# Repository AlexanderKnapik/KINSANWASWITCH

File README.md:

# KINSANWASWITCH

DIY-friendly photointerrupter microswitch/lamp holder 2-in-1 for generic 100mm Chinese arcade buttons. Enables an OBSA-LHSXF+OBSA-100UMQ-like setup at low cost with generic parts.

## Updates
- This is branch of beta-version SHINSANWASWITCH update version 1.1 with some optimizations that needs to be verified, so now everything is divided into two branches: *main* with stable version 1.0 and version1.1 in *beta* . If you want currently stable version - use *main* branch. 
Version 1.1 has some optimizations in body of SHINSANWASWITCH and possibility to make different variants of PCB to make with possibility to make one-layered-board at home (if you have enough skill). More info here:  https://www.projectdiva.net/community/threads/shinsanwaswitch-blog-of-creating-diy-analog-of-obsa-lhsxf-ln.2325/page-2#post-18644

## Parts list

### Electrical
Details about PCB and it's variants can be found in [readme in pcb thread](pcb/README.md)

- PCB: 1x `PCB` **1mm thickness** (KiCad 5.99+ (5.99.0-12455-g28bd734313), release build required for exporting Gerber files or take Gerber files archive in `gerber/shinsanwaswitch.zip`)
  - C1: Generic 0.1uF through hole ceramic capacitor.
  - C2: *not necessary, but recommended* 47uF 6.3v electrolitic capacitor on the power line input (read [some nuances of board assembly](https://github.com/steelpuxnastik/SHINSANWASWITCH/tree/version1.1/pcb#some-nuances-of-board-assembly) for more ditails)
  - STI1: `NSI45020AT1G` (for standard and one-layered-board with LED driver board versions) or R4: 470ohm 5% 1/4W through hole (for one-layered-board with resistor and 12v power-up 20mA LED, in other case use calculation to know what resistor you need to use)
  - J1: `S5B-PH-K-S` or equivalent.
  - LED: `S2B-PH-K-S` or equivalent.
  - PC1: `RPI-352`.
  - Q1: `2SC5395-F` or equivalent (may be rare but can be found on e.g. aliexpress).
  - R1: 330ohm 5% 1/4W through hole.
  - R2: 22kohm 5% 1/4W through hole.
  - R3: 10kohm 5% 1/4W through hole.
- 1x harness
  - 5x Single-ended **JST PH** wires (can be found on e.g. aliexpress or alternatively you can crimp them yourself, I recommend you to found on aliexpress for it 5pin 22 AWG white-blue-red-green-black cable, it amazingly fits connector, feels very reliable and also fits into the understandable color scheme)
  - 1x JST `PHR-5` or equivalent.
- 1x LED assembly (no resistors required)
  - 2x **JST PH** to **.1" (BLS-02/Dupont 2pin) female** wires (can be found on e.g. aliexpress or alternatively you can crimp them yourself. I recommend to use wires flexible as possible, that will be very useful. Wires length - somewhere around ~150-160mm, need be shorter as possible, because long wires will be nowhere to fold. Can be made by soldering single-ended JST PH wire and .1" (BLS-02/Dupont 2pin) female wire together and wrapping each wire with heat shrink tubing).
  - 1x 20mA through hole white LED (plugs into the .1" (BLS-02/Dupont 2pin) female connector).
  - 1x JST `PHR-2` or equivalent.
  - 1x 2 pin .1" (BLS-02/Dupont 2pin) female connector housing.
  
### Pin mapping

I/O port (from up to down):

| \#  | Description |
| --- | ----------- |
|  1  | LED+ |
|  2  | LED- |
|  3  | +5V |
|  4  | OUT |
|  5  | GND |

LED connector (from up to down):

| \#  | Description |
| --- | ----------- |
|  1  | + |
|  2  | - |

### Mechanical

- 3D printable parts (printing in resin recommended for best accuracy but not required)
  - 1x `STL/body.STL`
  - 1x `STL/cap.STL`
  - 3x `STL/lever_*.STL` (because of possible differences of generic 100mm Chinese arcade buttons and possible differences in preferences of players that will use it there available 3 different lengts of levers that you should print separately (and better in different colors) and then determine from your own experience what is best for you)
	- 1x `STL/lever_long.STL`
	- 1x `STL/lever_middle.STL`
	- 1x `STL/lever_short.STL`
- 1x 0.3x6x10mm (wire thickness x outer diameter x length) spring (can be found on e.g. aliexpress).
- 2x M2x8 screws

### Example of 3D-print settings that were used
- Layer height: 0.12mm (can be less, but not more, because quality depends on it)
- Nozzle: 0,4mm (can be less, of course)
- Fill level: 25%
- Number of wall lines: 4
- Number of cover layers: 4
- Number of bottom layers: 4
- Supports: only from the bed
- Filament: PETG
- Color: any, but the lever must be black or the part of lever that crosses the optocoupler must be painted with a marker in black in several layers, otherwise the optocoupler will work incorrectly and the switch will not work correctly.

## Source files
In folder `source` there are available source files that used to create 3D-models in SolidWorks. You can use them to make your modification, if you need it.

Original 100mm arcade button Solidworks source files taken from https://grabcad.com/library/100mm-button-1 and very helped me to make this thing.

# Known issues 
At this moment there is no possibility to connect SHINSANWASWITCH (and its active board) to regular matrices, where used connection between different pins, but not pin to ground that used here. If you know how to get around this problem - please, write about that in our issues thread: https://github.com/steelpuxnastik/SHINSANWASWITCH/issues/1

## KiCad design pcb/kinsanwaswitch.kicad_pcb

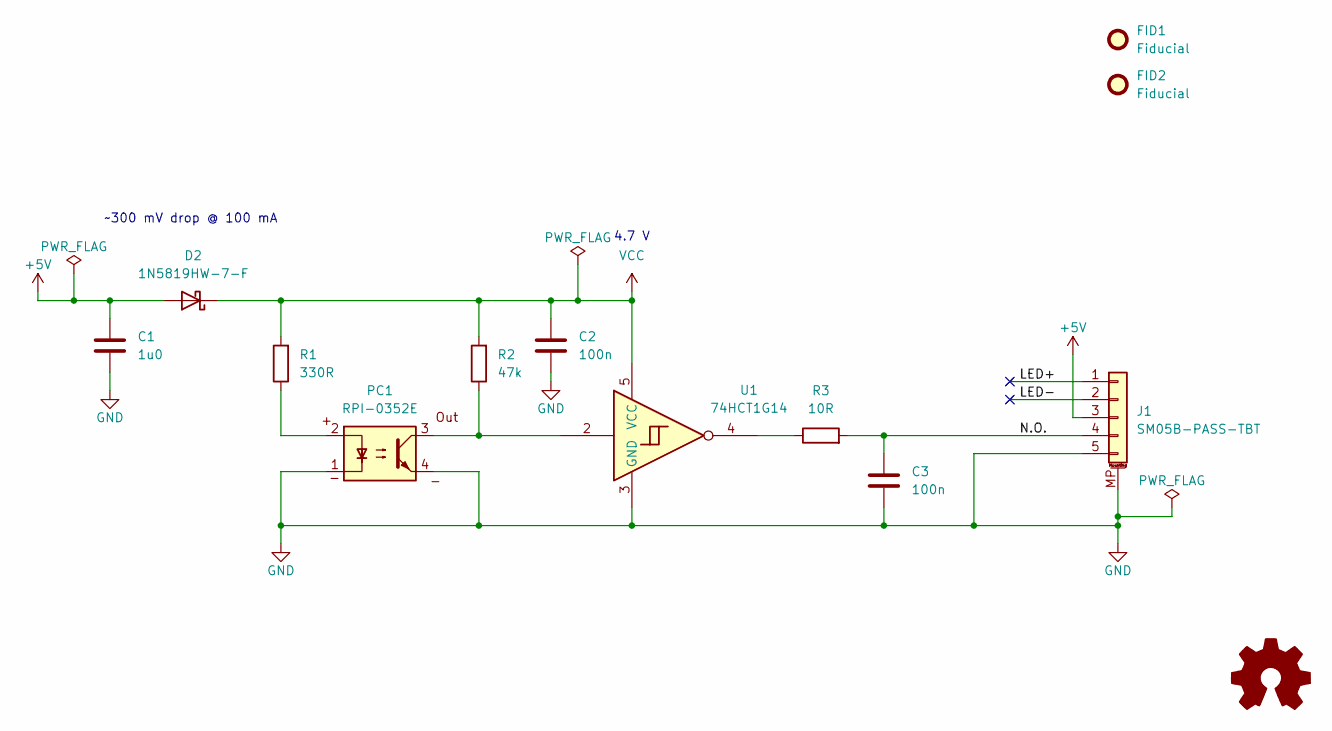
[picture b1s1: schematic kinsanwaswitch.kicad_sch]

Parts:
C1: 1u0; C_0603_1608Metric
C2, C3: 100n; C_0603_1608Metric
D2: 1N5819HW-7-F; D_SOD-123
FID1, FID2: Fiducial; Fiducial_0.5mm_Mask1mm
J1: SM05B-PASS-TBT; JST_PH_S5B-PH-SM4-TB_1x05-1MP_P2.00mm_Horizontal
PC1: RPI-0352E; Rohm_RPI-0352E
R1: 330R; R_0603_1608Metric
R2: 47k; R_0603_1608Metric
R3: 10R; R_0603_1608Metric
SYM1: Logo_Open_Hardware_Small; OSHW-Logo_5.7x6mm_SilkScreen
U1: 74HCT1G14; SC-74A-5_1.55x2.9mm_P0.95mm

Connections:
+5V: C1.1, D2.2 (A), J1.3
/LED+: J1.1
/LED-: J1.2
/N.O.: C3.1, J1.4, R3.2
GND: C1.2, C2.2, C3.2, J1.5, J1.MP (MountPin), PC1.1, PC1.4, U1.3 (GND)
unnamed: PC1.2, R1.1
unnamed: PC1.3, R2.1, U1.2
unnamed: R3.1, U1.4
VCC: C2.1, D2.1 (K), R1.2, R2.2, U1.5 (VCC)

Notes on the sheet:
4.7 V
~300 mV drop @ 100 mA

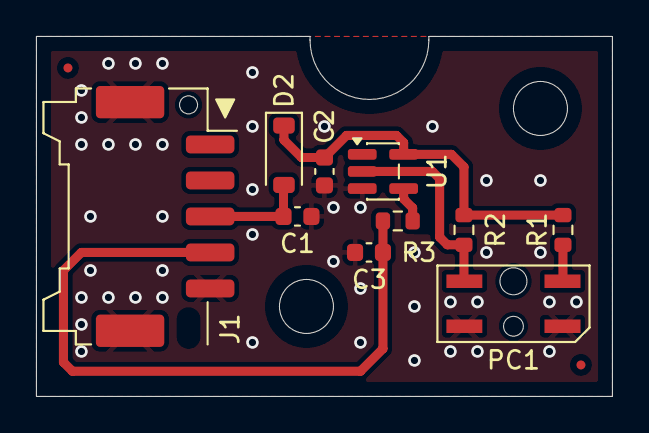
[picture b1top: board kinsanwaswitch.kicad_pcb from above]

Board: 2 copper layers, 32.0 x 20.0 mm, 13 parts (1 on the bottom side), 7 nets.

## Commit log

2025-09-06 new hardware design
    Using a schmitt trigger inverter over the second open collector NPN
    transistor. Redid the PCB layout to use surface mount components over
    through hole and aligned all components to a grid.
2025-09-06 add name and dates to sheets
2025-09-06 rearrange folder structure
    Split the source folder into the mechanicals (mech) and the images in
    the README.md file (docs).
2025-09-17 generate pcb 3d step file
2025-09-17 3d model samducksa cwb 401 switch
2025-12-06 initial enclosure modelling
    Modelled the spring plunger and the PCB cavity so far.
2025-12-06 model cwb401 lamp holder
2025-12-06 revision 1.0 PCB
